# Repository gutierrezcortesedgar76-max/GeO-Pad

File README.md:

# GeO-Pad
A 3 key macropad with a pet that you can see while playing Geometry Dash or use for other things. The reason I made this is because, while playing, my wrist gets stabbed by the corners of my laptop and develops bruises so it allows users to play comfortably without hurting their wrist on laptop corners such as me and allows easy portability unlike a 60% mechanical keyboard. It includes a oled screen so you can have a little pet while raging and making stuff.
# Software
1. KiCad-I used KiCad to actually design the Schematic and the PCB itself
2. PyCharm-This is where I wrote the code for the GeO-Pad while following tutorials on youtube (first time coding)
3. Onshape- I used this to model the case and to import the model, https://cad.onshape.com/documents/ef6d16a207c5b8c174a817fd/w/876528ba5902b90e52078595/e/ea60b42722162e659b97915d?renderMode=0&uiState=6ade0d7e211ee294f06135e0
# Instructions
1.Save the standard ssd1306.py driver module to your RP2040 device via Thonny or VS Code.
2.Flash the above script as main.py to run automatically on startup.
# A.I usage
Along with the coding tutorials I watched, I used Gemini to check my code for any mistakes and I would fix it with the suggestions from Gemini. During the revision process, I used Gemini as a second set of eyes to check my connections of the board. 
## Geo-Pad – Bill of Materials

| Week | Tier | Parts funding |
| :--- | :--- | :--- |
| Week 1 | Tier 1 | $30.00 |

| Part | What it's for | Qty | Unit | Total | Vendor |
| :--- | :--- | :--- | :--- | :--- | :--- |
| [RP2040 pro micro](https://github.com/gutierrezcortesedgar76-max/GeO-Pad/blob/main/BOM.md#https://www.aliexpress.us/item/3256806781060135.html?src=google&src=google&albch=shopping&acnt=708-803-3821&isdl=y&slnk=&plac=&mtctp=&albbt=Google_7_shopping&aff_platform=google&aff_short_key=UneMJZVf&gclsrc=aw.ds&albagn=888888&ds_e_adid=&ds_e_matchtype=&ds_e_device=c&ds_e_network=x&ds_e_product_group_id=&ds_e_product_id=en3256806781060135&ds_e_product_merchant_id=5762056048&ds_e_product_country=US&ds_e_product_language=en&ds_e_product_channel=online&ds_e_product_store_id=&ds_url_v=2&albcp=19558607238&albag=&isSmbAutoCall=false&needSmbHouyi=false&gad_source=1&gad_campaignid=19566915268&gbraid=0AAAAAD6I-hHFuM5JDl6TUJptf0ACTEZmz&gclid=CjwKCAjw25fWBhAVEiwAMopNjlyufh_ijJvVy_PywzVok832ihfuf9-1KMYrm4mJodwwldlTehrMBhoCP3MQAvD_BwE&gatewayAdapt=glo2usa) | The main brain for the project! | 1 | $2.00 | $2.00 | [Aliexpress](https://github.com/gutierrezcortesedgar76-max/GeO-Pad/blob/main/BOM.md#https://www.aliexpress.us/item/3256806781060135.html?src=google&src=google&albch=shopping&acnt=708-803-3821&isdl=y&slnk=&plac=&mtctp=&albbt=Google_7_shopping&aff_platform=google&aff_short_key=UneMJZVf&gclsrc=aw.ds&albagn=888888&ds_e_adid=&ds_e_matchtype=&ds_e_device=c&ds_e_network=x&ds_e_product_group_id=&ds_e_product_id=en3256806781060135&ds_e_product_merchant_id=5762056048&ds_e_product_country=US&ds_e_product_language=en&ds_e_product_channel=online&ds_e_product_store_id=&ds_url_v=2&albcp=19558607238&albag=&isSmbAutoCall=false&needSmbHouyi=false&gad_source=1&gad_campaignid=19566915268&gbraid=0AAAAAD6I-hHFuM5JDl6TUJptf0ACTEZmz&gclid=CjwKCAjw25fWBhAVEiwAMopNjlyufh_ijJvVy_PywzVok832ihfuf9-1KMYrm4mJodwwldlTehrMBhoCP3MQAvD_BwE&gatewayAdapt=glo2usa) |
| [DO-35 Diodes](https://github.com/gutierrezcortesedgar76-max/GeO-Pad/blob/main/BOM.md#https://www.amazon.com/1N4148-Sealed-Switching-Electronic-Silicon/dp/B0DS1JLQ1X?th=1) | DC current | 1 | $4.00 | $4.00 | [amazon](https://github.com/gutierrezcortesedgar76-max/GeO-Pad/blob/main/BOM.md#https://www.amazon.com/1N4148-Sealed-Switching-Electronic-Silicon/dp/B0DS1JLQ1X?th=1) |
| [128x64 oled screen](https://github.com/gutierrezcortesedgar76-max/GeO-Pad/blob/main/BOM.md#https://geekworm.com/products/0-96-inch-oled?srsltid=AU7gw4X4595XJoicfSWN-w5RxvtSj3fx9DkIDwHyd9mX74WIFRMzGBiPOB4) | display | 1 | $5.00 | $5.00 | [geekworm](https://github.com/gutierrezcortesedgar76-max/GeO-Pad/blob/main/BOM.md#https://geekworm.com/products/0-96-inch-oled?srsltid=AU7gw4X4595XJoicfSWN-w5RxvtSj3fx9DkIDwHyd9mX74WIFRMzGBiPOB4) |
| **Parts subtotal** | — | — | — | **$11.00** | — |
| **Tax & shipping** | — | — | — | **$0.00** | — |
| **Total** | — | — | — | **$11.00** | — |

This Image depicts the PCB layout of the main board with the connections and the components 

This is the schematic drawing and depicts how every component is connected to each other through wiring

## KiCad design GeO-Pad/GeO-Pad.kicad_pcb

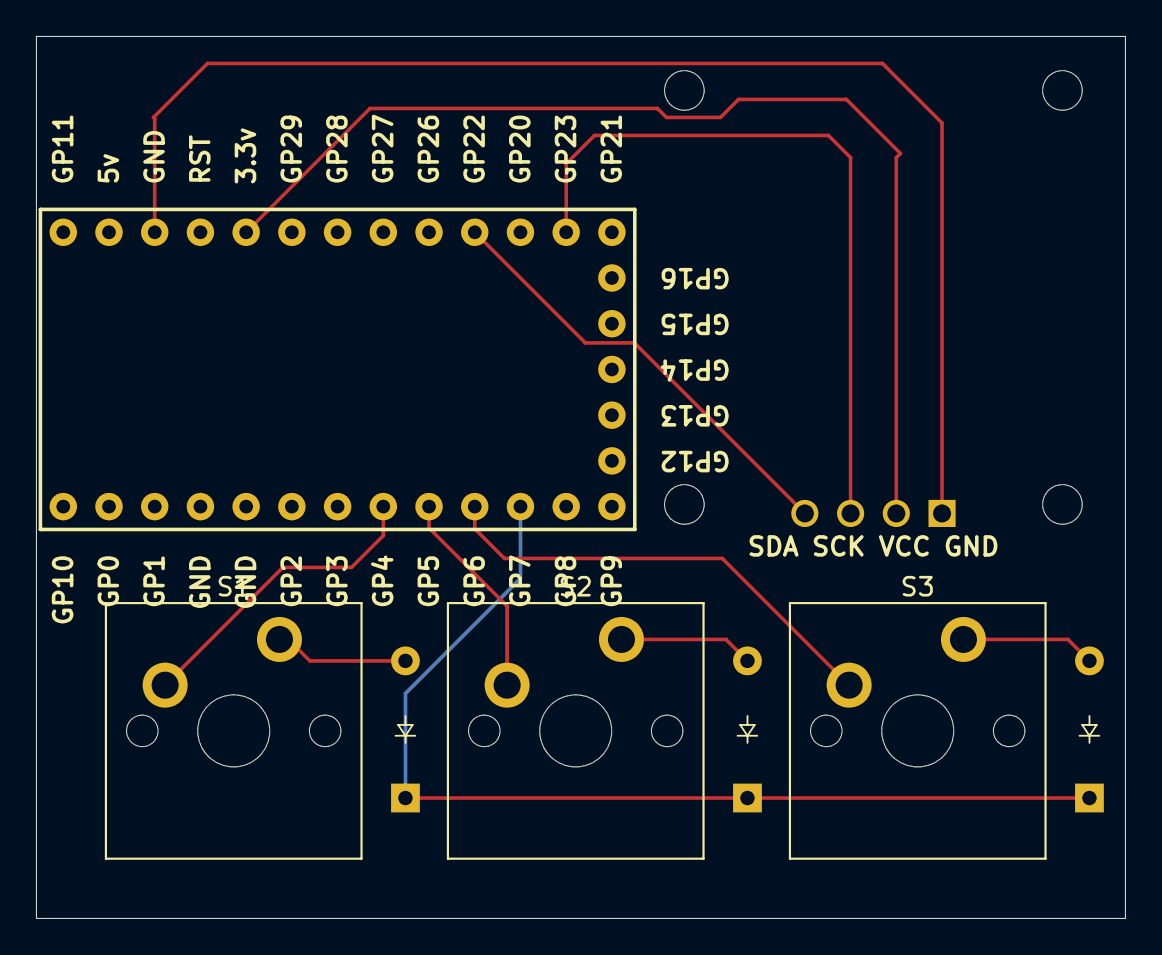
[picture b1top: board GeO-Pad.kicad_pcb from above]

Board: 2 copper layers, 60.5 x 49.0 mm, 8 parts (0 on the bottom side), 11 nets.

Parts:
D1, D2, D3: Diode_DO-35
J2: OLED_128x64
S1, S2, S3: MX_PCB_1.00u
U1: RP2040_Pro_Micro

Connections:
unnamed: D1.2 (A), S1.2
unnamed: D1.1 (K), D2.1 (K), D3.1 (K), U1.11 (GP7)
unnamed: D2.2 (A), S2.2
unnamed: D3.2 (A), S3.2
unnamed: J2.1 (GND), U1.29 (GND)
unnamed: J2.3 (SCL), U1.20 (GP23)
unnamed: J2.4 (SDA), U1.22 (GP22)
unnamed: J2.2 (VCC), U1.27 (3.3v)
unnamed: S1.1, U1.8 (GP4)
unnamed: S2.1, U1.9 (GP5)
unnamed: S3.1, U1.10 (GP6)
